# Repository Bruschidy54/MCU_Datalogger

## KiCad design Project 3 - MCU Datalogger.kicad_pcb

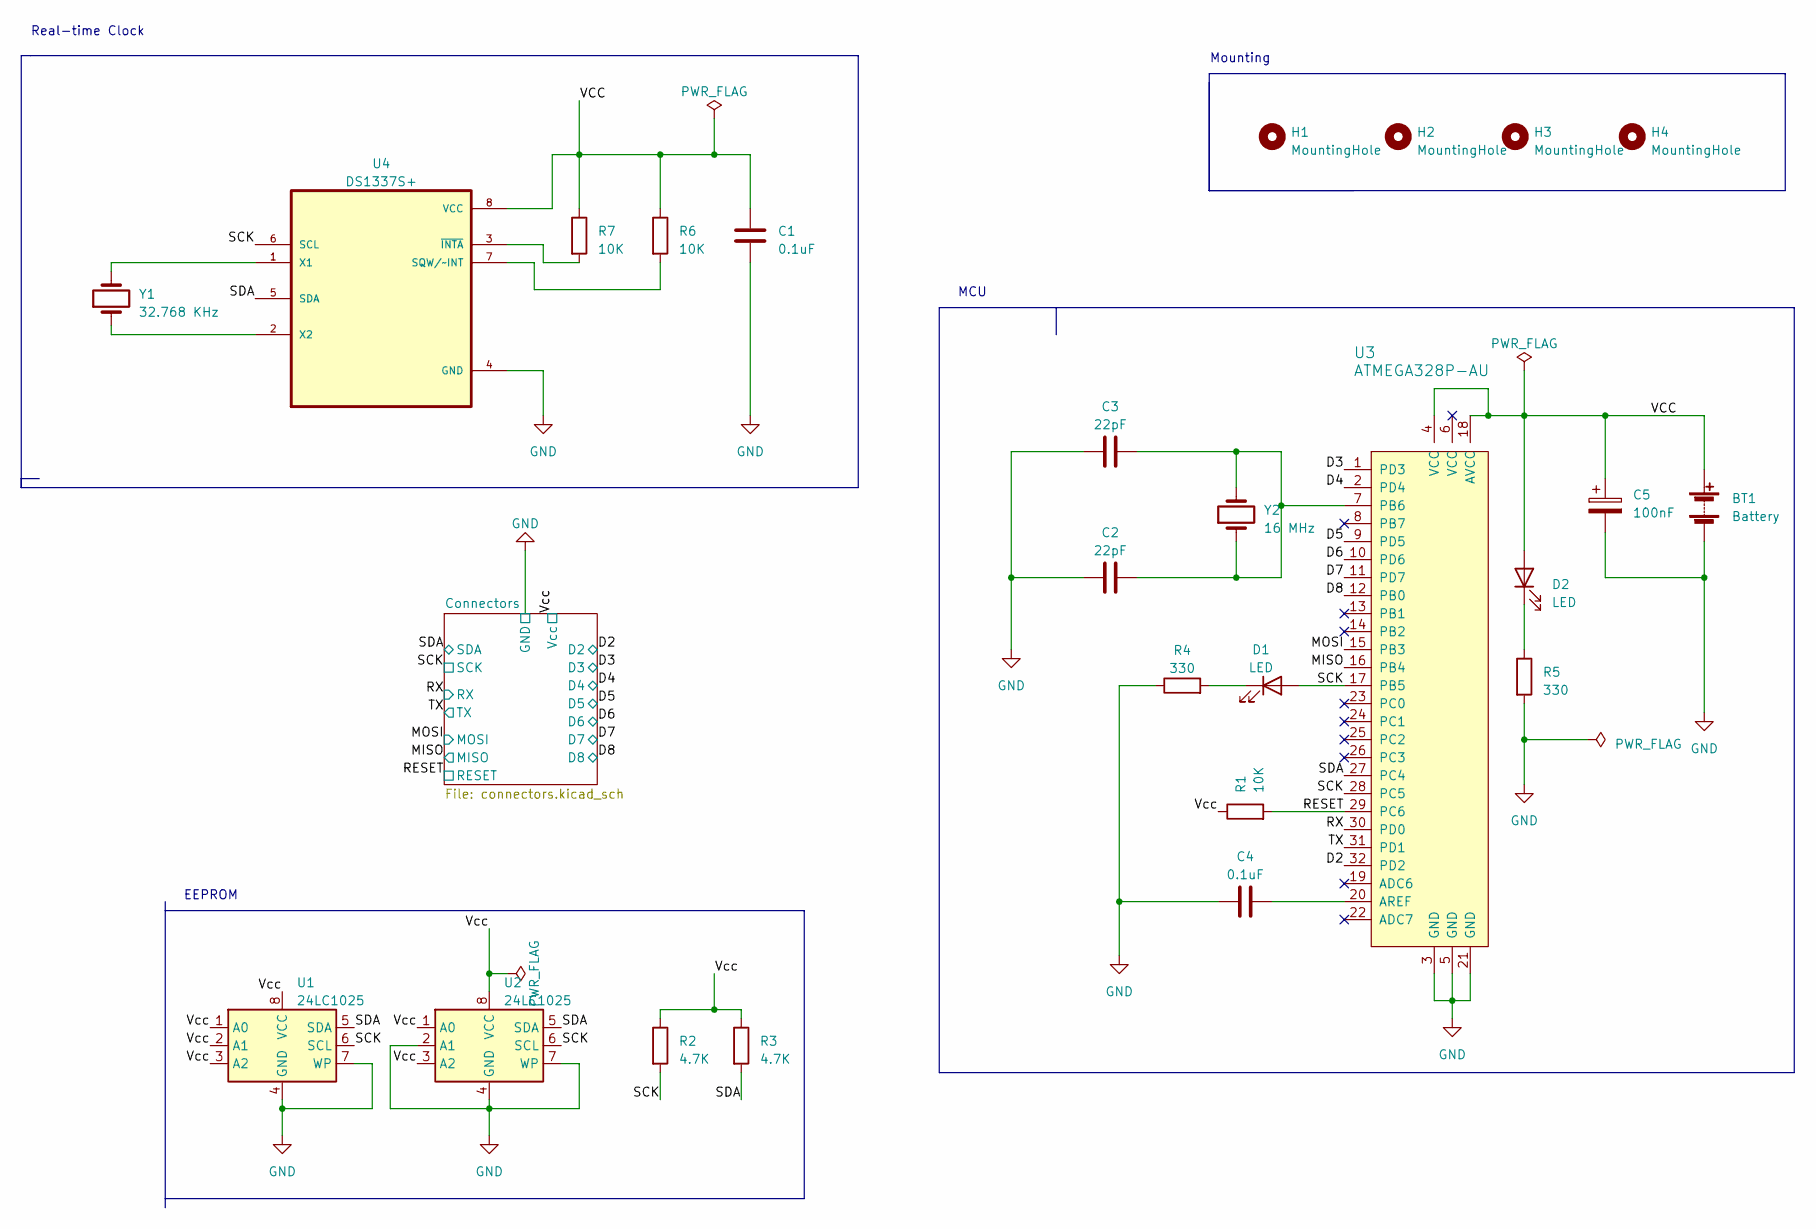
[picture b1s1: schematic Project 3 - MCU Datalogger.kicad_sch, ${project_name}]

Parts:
BT1: Battery; PinHeader_1x02_P2.54mm_Vertical
C1, C4: 0.1uF; C_0805_2012Metric
C2, C3: 22pF; C_0805_2012Metric
C5: 100nF; C_0805_2012Metric
D1, D2: LED; LED_0805_2012Metric
H1, H2, H3, H4: MountingHole; MountingHole_2.1mm
R1, R6, R7: 10K; R_0805_2012Metric
R2, R3: 4.7K; R_0805_2012Metric
R4, R5: 330; R_0805_2012Metric
U1, U2: 24LC1025; SOIC-8_5.23x5.23mm_P1.27mm
U3: ATMEGA328P-AU; QFP80P900X900X120-32N; MPN ATMEGA328P-AU; Digi-Key_PN ATMEGA328P-AU-ND
U4: DS1337S+; SOIC127P600X175-8N
Y1: 32.768 KHz; Crystal_SMD_5032-2Pin_5.0x3.2mm_HandSoldering
Y2: 16 MHz; Crystal_SMD_5032-2Pin_5.0x3.2mm_HandSoldering

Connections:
/D2: U3.32 (PD2); also elsewhere on the board
/D3: U3.1 (PD3); also elsewhere on the board
/D4: U3.2 (PD4); also elsewhere on the board
/D5: U3.9 (PD5); also elsewhere on the board
/D6: U3.10 (PD6); also elsewhere on the board
/D7: U3.11 (PD7); also elsewhere on the board
/D8: U3.12 (PB0); also elsewhere on the board
/MISO: U3.16 (PB4); also elsewhere on the board
/MOSI: U3.15 (PB3); also elsewhere on the board
/RESET: R1.2, U3.29 (PC6); also elsewhere on the board
/RX: U3.30 (PD0); also elsewhere on the board
/SCK: D1.2 (A), R2.2, U1.6 (SCL), U2.6 (SCL), U3.17 (PB5), U3.28 (PC5), U4.6 (SCL); also elsewhere on the board
/SDA: R3.2, U1.5 (SDA), U2.5 (SDA), U3.27 (PC4), U4.5 (SDA); also elsewhere on the board
/TX: U3.31 (PD1); also elsewhere on the board
/VCC: BT1.1 (+), C1.1, C5.1, D2.2 (A), R6.1, R7.1, U3.4 (VCC), U3.18 (AVCC), U4.8 (VCC)
/Vcc: R1.1, R2.1, R3.1, U1.1 (A0), U1.2 (A1), U1.3 (A2), U1.8 (VCC), U2.1 (A0), U2.3 (A2), U2.8 (VCC); also elsewhere on the board
GND: BT1.2 (-), C1.2, C2.1, C3.1, C4.1, C5.2, R4.1, R5.2, U1.4 (GND), U1.7 (WP), U2.2 (A1), U2.4 (GND), U2.7 (WP), U3.3 (GND), U3.5 (GND), U3.21 (GND), U4.4 (GND); also elsewhere on the board
unnamed: D1.1 (K), R4.2
unnamed: D2.1 (K), R5.1
unnamed: C4.2, U3.20 (AREF)
unnamed: C2.2, C3.2, U3.7 (PB6), Y2.1, Y2.2
unnamed: R6.2, U4.7 (SQW/~INT)
unnamed: U4.1 (X1), Y1.2
unnamed: U4.2 (X2), Y1.1
unnamed: R7.2, U4.3 (~INTA)

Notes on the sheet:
Mounting
Real-time Clock
MCU
EEPROM

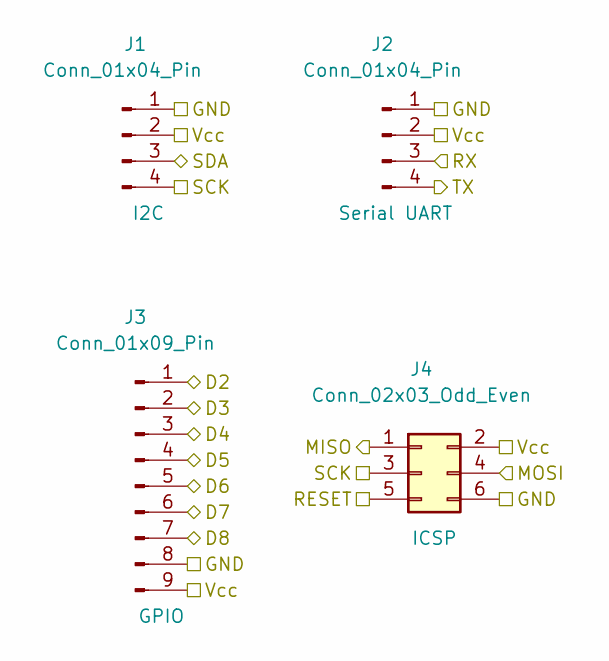
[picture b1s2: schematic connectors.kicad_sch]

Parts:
J1, J2: Conn_01x04_Pin; PinHeader_1x04_P2.54mm_Vertical
J3: Conn_01x09_Pin; PinHeader_1x09_P2.54mm_Vertical
J4: Conn_02x03_Odd_Even; PinHeader_2x03_P2.54mm_Vertical

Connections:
/D2: J3.1; also elsewhere on the board
/D3: J3.2; also elsewhere on the board
/D4: J3.3; also elsewhere on the board
/D5: J3.4; also elsewhere on the board
/D6: J3.5; also elsewhere on the board
/D7: J3.6; also elsewhere on the board
/D8: J3.7; also elsewhere on the board
/MISO: J4.1; also elsewhere on the board
/MOSI: J4.4; also elsewhere on the board
/RESET: J4.5; also elsewhere on the board
/RX: J2.3; also elsewhere on the board
/SCK: J1.4, J4.3; also elsewhere on the board
/SDA: J1.3; also elsewhere on the board
/TX: J2.4; also elsewhere on the board
/Vcc: J1.2, J2.2, J3.9, J4.2; also elsewhere on the board
GND: J1.1, J2.1, J3.8, J4.6; also elsewhere on the board

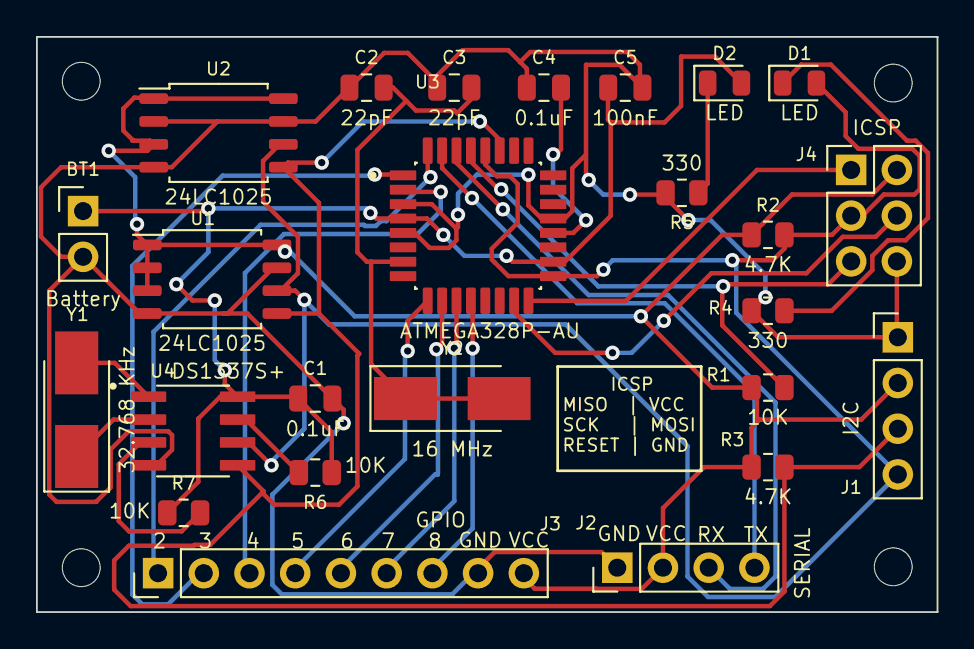
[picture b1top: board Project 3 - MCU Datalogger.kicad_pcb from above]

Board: 2 copper layers, 50.0 x 32.0 mm, 29 parts (0 on the bottom side), 25 nets.

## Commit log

2023-08-18 Setup of EESchema
2023-08-18 Added symbols to schema
2023-08-18 Added symbols to schema (forgot to do this last time)
2023-08-18 arranged symbols in schema
2023-08-18 added component values in schema
2023-08-18 Assigned footprints to symbols
2023-08-21 completed writing in schematic sheet 1
2023-08-21 completed writing of embedded connector sheet
2023-08-21 assigned power nets and added comments
2023-08-21 Imported symbols into pcb new and updated power net class properties
2023-08-22 placed footprints onto pcb design
2023-08-22 wired 2 layer pcb
2023-08-22 fixed wiring violations and added silkscreen labels
2023-08-22 add board characteristics and 3d models
2023-08-22 missing updates
